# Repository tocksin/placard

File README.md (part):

# Placard
## PLA computer
This project is a computer designed using some Programmable Logic Arrays (PLA) 
or Programable Array Logic (PAL) or Programmable Array Devices (PLD) chips.  
This started as a pure 7400-series chip computer, but changed over to using 
some PLA/PLDs to increase the usability while not greatly increasing the chip 
count.  The first PLA was created in 1970 by Texas Instruments.  The PAL was 
created in 1978 by Monolithic Memories which is owned by Lattice Semi today. 
There are some differences between the three types of chips, but this project 
isn't going to distinguished between them.

The design documents are in [docs/](docs/README.md), grouped by subject.

## Project goals
The project has some hard-goals to maintain:
- Use only through-hole chips similar to the 7400-series DIP chips (or PLA of course)
- Use only active production chips.  No hunting sketchy websites for parts.
- Design true von Neumann CPU from scratch.  No Harvard.  Bare-metal programming on the computer is a must (native compiler).
- Have a video output.  The video standard is open, but probably a legacy output (VGA/Composite/etc).
- Make the instruction set "fun" to program.  This means no racing the beam to draw the screen.  Counting instructions is not fun.
- A PS/2 keyboard and mouse, read by the machine's own PLD receiver.  No USB.
- Native storage capabilities.  Need to be able to save/load programs as you create them on the computer.

## Block diagram
Each block shows how many chips it uses (33 and a 3.3 V regulator on the main board; the expansion and cartridge slots add none, the cartridge itself has 5).  See [docs/architecture/CHIPS.md](docs/architecture/CHIPS.md) for the parts.

The drawing is made by `src/scripts/gen_block_diagram.py` (CPU on the left, memory, I/O and audio in the middle, video on the right); rerun it when the design changes.

The I/O circuitry (SNES pads, SD card, PS/2 keyboard and mouse) is drawn as a schematic in
[docs/architecture/IO.md](docs/architecture/IO.md#schematic) (`schematics/placard_io_schematic.png`).
The audio circuitry (sample read, DAC register, R-2R ladder, audio line out jack) is drawn in
[docs/sound/SOUND.md](docs/sound/SOUND.md#schematic) (`schematics/placard_video_audio_schematic.png`).

The real schematic and PCB layout are a KiCad project in [kicad/](kicad/).

To build a board one chip at a time, testing each with a multimeter as it goes in, follow [docs/hardware/BRINGUP.md](docs/hardware/BRINGUP.md); it has a bring-up test ROM that checks the CPU and memory and shows the I/O on the screen.

## Memory Map
The Placard has 64kB of memory arranged in a 16-bit address bus and 8-bit databus.  The video RAM starts at x6020 and ends at xFFFF, and each row's mode byte (color mode and line repeat) is at x5A20 + row.  There is a 64kB RAM and a 64kB ROM behind the same addresses.  The address space is divided into eight 8kB sections, and a write-only map register at x5000 picks whether each section reads from the RAM or the ROM.

- **Writes always go to the RAM**, even in a section mapped to ROM.  The write strobe (/WE) is not decoded by address, so a write in the I/O window x5000-x53FF also lands in the RAM underneath it.
- **The map register** is a CD74ACT273E clocked by /MAP_WR from the I/O decode PLD; it latches the source bus at the end of the write.  Bit n = 1 makes section n read from RAM, 0 from ROM.  Bit 2 maps x4000-x4FFF and x5400-x5FFF, because x5000-x53FF is the I/O window.  It is write only, so software keeps a copy of the last value it wrote.
- **At power-up every section reads as ROM.**  RUN from the ROM cartridge holds the register's /MR low while the cartridge loads its SRAM and the CPU is held, so the CPU boots from ROM ([docs/architecture/ROM.md](docs/architecture/ROM.md#loading-the-cartridge)).
- **x5000-x53FF is the I/O window.**  The memory control PLD keeps both the RAM and the ROM off the bus there, so I/O always has priority.
- **Only `[Y,X]` reaches the I/O window**; `[0,D]` and `[0,X]` only address the zero page.
- **Video reads always read the RAM** (memory control PLD); only CPU reads follow the map.  The CPU can run code from the ROM under the video area while the screen shows the RAM, and a program that wants to read the video RAM maps that section to RAM.
- **The ROM is grouped by 8 KB section.**  The machine's 32K ROM (x8000-xFFFF, read at x0000-x7FFF too) holds the boot loader, the library, BASIC and a loader that runs the DOS and programs from the SD card, and each map section holds one kind of thing: section 7 what almost every program uses (jump table, core routines, PS/2 keyboard, pads, mouse, line input), section 6 the files (SD card driver, FAT reader and writer), section 5 BASIC, section 4 the loader, sound driver and font.  A program that maps a section to RAM gives up just that; the font is read through a zero page pointer (`FONT_PG`), so a program can put its own font anywhere.  The library runs in place.  The boot loader copies the library's RAM code to x1F00, gives each expansion card a chance to run its own boot code (like the Apple II), then maps sections 0 and 2 to RAM (map = 05) and starts the loader.  A development ROM (64K cartridge) adds one program in the first 32K, run in place at x6000-x7FFF and x2000-x3FFF, or copied to RAM x0000 for the older demos.  See [docs/architecture/ROM.md](docs/architecture/ROM.md) and [docs/software/DOS.md](docs/software/DOS.md).
- **After a map write**, the next instruction must not be fetched from a section whose map bit that write changed, unless the ROM and RAM hold the same byte there (the new map arrives 2.6 ns too late for that fetch).  Copying the ROM into the RAM underneath and then switching the section is safe.  See [docs/timing/TIMING.md](docs/timing/TIMING.md#video-and-the-rest).

The memory control PLD (`ATF22V10_MEM_CTRL.pld`) makes /ROM_OE and /RAM_OE from the address, the map, RW and PIXEL_ENABLE, using only the low half of each clock.  The RAM's /WE comes from the Sync PLD, off an early tap of the clock ([docs/timing/WE_TIMING.md](docs/timing/WE_TIMING.md)).  The I/O decode PLD (`ATF22V10_IO_DECODE.pld`) makes the upper RAM/ROM chip select (/CE_HI) and the I/O strobes.

The RAM is two AS7C256C-15PCN (32K × 8, 15 ns) chips.  The ROM is two more AS7C256C-15PCN on the ROM cartridge, loaded at power-up from two AT28C256 EEPROMs by the cartridge while it stalls the CPU ([docs/architecture/ROM.md](docs/architecture/ROM.md#loading-the-cartridge)).  See [docs/architecture/CPU.md](docs/architecture/CPU.md#memory-parts) and [docs/timing/TIMING.md](docs/timing/TIMING.md).

| Address | Map bit | Function  |
|---------|---------|------|
| x0000-x1FFF | 0 | RAM/ROM (zero page, program variables, library RAM code at x1F00; ROM: reset jump) |
| x2000-x3FFF | 1 | RAM/ROM (development ROM: program) |
| x4000-x4FFF | 2 | RAM/ROM (program data; FAT variables and buffer at x4D00-x4FFF) |
| x5000-x53FF | none | I/O window (see below) |
| x5400-x5FFF | 2 | RAM/ROM (mode bytes at x5A20-x5BFF, audio buffer at x5DF3-x5FFF) |
| x6000-x7FFF | 3 | RAM/ROM (Video Memory from x6020; development ROM: program from x6000) |
| x8000-x9FFF | 4 | RAM/ROM (Video Memory; ROM: vectors x8000, loader and the end of BASIC x8100, sound driver x9200, font x9700, LIB_RAM copy x9F00) |
| xA000-xBFFF | 5 | RAM/ROM (Video Memory; ROM: BASIC) |
| xC000-xDFFF | 6 | RAM/ROM (Video Memory; ROM: files: SD card driver xC000, FAT reader xC800, FAT writer xD600) |
| xE000-xFFFF | 7 | RAM/ROM (Video Memory; ROM: PS/2 keyboard, pads, mouse, line input, menu hook, slot helpers, core routines xF400, jump table xFB00, boot loader xFD00) |

The drawing is made by `src/scripts/gen_memory_map.py`; rerun it when the map changes.

### I/O window
Each I/O page has its own select from the I/O decode PLD (revision 07), made straight from the address and valid about 13 ns into the clock.  A write is the select with /WE: devices latch the source bus on the rising edge at the end of /WE.  A read is the select with Q0 low (the LOAD_MEM clock, when the CPU latches the bus into D), and nothing waits for STALL.  The shared port is described in [docs/architecture/IO.md](docs/architecture/IO.md) and the expansion slots in [docs/architecture/EXPANSION.md](docs/architecture/EXPANSION.md).

| Address | Select | R/W | Function |
|---------|--------|-----|----------|
| x5000-x50FF | /P0 (write: /MAP_WR from the Sync PLD) | W | ROM/RAM map register (built) |
| x5000-x50FF | /P0 and Q0 | R | Video line counter, V9:V2 (built) |
| x5100-x517F | /EXP1 | R/W | Expansion slot 1 |
| x5180-x51FF | /EXP3 | R/W | Expansion slot 3 |
| x5200-x52FF | /PORT and /WE | W | Shared port latch (port PLD registers): SD card SCK, MOSI and /CS, SNES pad clock and latch, PS/2 lines; a write to x5202/x5203 also re-arms the PS/2 receiver |
| x5200-x52FF | /PORT and Q0 | R | Shared port: SD MISO and the free PS/2 clock (x5200), SNES pad data (x5201), PS/2 receiver byte (x5202) and ready flag (x5203) |
| x5300-x537F | /EXP2 | R/W | Expansion slot 2 |
| x5380-x53FF | /EXP4 | R/W | Expansion slot 4 |

### Sound
The video circuit reads one 8-bit sample per scan line from x5DF3-x5FFF (525 bytes, one frame) and plays it through a 74HCT574 and a resistor ladder DAC, at the line rate of 31.47 kHz.  80h is silence.  The library's sound driver (`snd_update` once a frame, with `snd_tone`, `snd_beep`, `snd_note`, `snd_noise` and `snd_play`) refills the buffer behind the line being played.  See [docs/sound/SOUND.md](docs/sound/SOUND.md).

### Video line read
A read anywhere in x5000-x50FF returns the upper 8 bits of the video line counter, V9:V2.  The V counter in the V Counter PLD counts 499 to 1023, and one 74F541 enabled by /P0 and Q0 puts V9:V2 on the data bus.  The ROM/RAM map register shares the page but is write only, so there is no conflict.  Read it with `ld 0x50, y` then `ld [y,x], ac`.

- **It is a single byte**, so it can't tear between reads.
- **Resolution is 4 lines** (128 us).  Visible rows start at V = 544, so `row / 4 = value - 136`.  A value below 136 means vertical blanking.
- **There is no frame counter.**  Software keeps time by polling: each time the value goes down (from 255 back to 124), a frame has passed.  At the FPGA's 25.000 MHz clock a frame is 525 lines, about 16.8 ms (59.5 Hz).
- **Software must poll at least once per frame**, or it misses a wrap.  Elapsed time is then frames x 16.8 ms plus the line position for finer detail.

## Video
The video is designed to be 640x480 VGA 60Hz standard.  This means a 25.175 MHz clock.  This requires two counters: a horizontal and vertical.  They count 800 and 600 pixels.  This needs a 10-bit counter for each.  The counters form the RAM address space to read the pixel values.  The video memory is organized in a non-traditional way with H,V instead of V,H.

### Line repeat
Bits 3:2 of a row's mode byte make each byte of video memory show on 1, 2 or 4 lines (640 × 480, 240 or 120).  A full 2x screen leaves 20 KB of the video area free (the even pages x60, x62 ... xFE) and a full 4x screen 30 KB.  The audio slot PLD remaps four row address bits, so no chips were added.  See [docs/video/VIDEO.md](docs/video/VIDEO.md#line-repeat).

### Text demo
`src/scripts/text_demo.asm` draws a demo screen with the CPU and keeps a test running on it: 80 column text (2 colors, 1x, on row tints: a blue status panel and a rainbow raster bar that bounces behind the text), a 16 color band (4 bpp, 4x), 40 column text (2 bpp, 2x) and a 256 color band (8 bpp, 4x) with "256" in shades of red, blue and green and a turning rainbow ring.  Each frame it tests one page of RAM (85 pages: x0100-x1EFF, x2000-x4FFF, x5400-x59FF and x5C00-x5CFF, 14 patterns each, with a progress bar, pass and error counts) and updates a frame counter, an uptime clock, a spinner, a turning color wheel, the ring and a message that scrolls a pixel a frame.  It runs from the SD card (`TEXT.PLC`, `gen_text_demo_sd.py`, in the demo menu), and `src/scripts/text_demo_sim.py` runs and checks it in the simulator (`--gif` makes an animation).  `gen_text_demo_sd.py` makes the SD card version (`TEXT.PLC`, in the demo menu), whose RAM test covers only the RAM the program leaves free ([docs/software/MENU.md](docs/software/MENU.md#the-text-demo-on-the-card)).

### DOS, BASIC and demo menu
The machine ships the 32K ROM image (`src/scripts/rom32.masm`, `build\rom32.bat`): the boot loader, the library, PLACARD BASIC (a 16-bit integer BASIC with strings, graphics, sound and SAVE/LOAD on the card, [docs/software/BASIC.md](docs/software/BASIC.md)) and a loader that runs `.PLC` programs from the SD card.  The DOS is one of those programs (`DOS.PLC`, `src/scripts/dos.masm`).  At power-up the loader runs the program named in `BOOT.CFG`, or the DOS's file browser (hold Esc) that runs, deletes and picks the boot program, with a command line for `LOAD` and `SAVE` of memory as files.  With no card, or no `DOS.PLC` on it, BASIC starts.  Ctrl+B in the browser starts BASIC.  The demo menu is one of those programs (`MENU.PLC`, `src/scripts/menu.masm`): the CPU test, pi, Mandelbrot, the Game of Life, the Boing ball, the 3D ships, the ray caster, the side scroller, the textured ray caster and the text demo run in turn, each until it is done or for 2 minutes (Mandelbrot 3); Esc in any program shows the menu (Up / Down and Enter, or 1-9 and 0), a program picked there runs until Esc, and after 2 minutes with no key the menu goes back to running them in turn.  The `sdcard/` folder holds the files for the card; `src/scripts/test_dos.py`, `test_menu.py` and `test_basic.py` check them in the simulator; the `.BAS` files on the card are BASIC examples.  See [docs/software/DOS.md](docs/software/DOS.md), [docs/software/MENU.md](docs/software/MENU.md) and [docs/architecture/ROM.md](docs/architecture/ROM.md#the-32k-image).

### Game demos
Four demos show what the CPU can do with no sprite or collision hardware.  The first three are written by a Python generator (the tables, the unrolled drawing code and a bit-exact model of the picture), and each has a simulator test that checks every frame against the model.

`sdcard/RAYCAST.PLC` (`gen_raycast.py`, which writes `src/scripts/raycast_sd.asm`) is a ray caster: an 80 × 112 view at 8 bpp (4x line repeat) of a maze with shaded, two-tone walls and a dithered floor and ceiling, walked by a demo script until a key or pad button takes over (arrow keys or SNES pad 1: Up / Down walk, Left / Right turn).  A view takes 143k-170k clocks (a column about 2,000), so it runs at the full 60 views a second using under 40 % of each frame.  It is in the demo menu and `src/scripts/test_raycast_sim.py` checks it.

`sdcard/RAYTEX.PLC` (`gen_raycast_tex.py`, with `RAYTEX.OVL`) is the same maze and demo walk with textured walls, in the style of Wolfenstein 3D: seven 32 × 32 textures drawn by the generator (stone, brick, wood, riveted metal, mossy stone, a circuit board with a 22V10 and a framed Mandelbrot picture), y sides darker than x sides and four levels of distance shading.  Each column finds where the ray hit the wall (two 8 × 8 multiplies), copies that texture column through a shading table into zero page, and draws the wall with a compiled scaler: one unrolled routine per wall height that stores the right texel into each cell.  A view takes 229k-261k clocks (about 3,000 a column), so it still runs at 60 views a second, with room left for sprites.  T turns the textures off (one flat, shaded color a wall) and on again.  `src/scripts/test_raycast_tex_sim.py` checks it.  It is in the demo menu: its textures and scalers go into the video RAM the screen leaves free ([docs/software/MENU.md](docs/software/MENU.md#the-ray-casters-and-the-scroller-on-the-card)).

`sdcard/SCROLLER.PLC` (`gen_scroller.py`, with `SCROLLER.OVL`) is a side-scrolling platformer at 160 × 112, 4 bpp: three parallax bands (clouds, mountains, hills at 1/8, 1/4 and 1/2 speed) over a tiled level, with a robot that runs, jumps, collects coins and stomps slimes, all at 60 frames a second.  The background is redrawn every frame by unrolled strips, top to bottom ahead of the beam, so nothing has to be erased.  The sprites are compiled: each frame of art is its own routine in RAM that stores its bytes (masked where a byte is half transparent) straight into video memory.  Background and sprites take about 93k of the 420k clocks in a frame.  The demo player plays until a key or pad button is pressed (arrow keys or SNES pad 1: Left / Right to run, Up, Space or pad B to jump).  `src/scripts/test_scroller_sim.py` checks it.  It is in the demo menu: its background strips go into the video RAM the screen leaves free ([docs/software/MENU.md](docs/software/MENU.md#the-ray-casters-and-the-scroller-on-the-card)).

`sdcard/WIRE3D.PLC` (`gen_wire3d.py`) is an Elite-style 3D demo and benchmark: six convex ships tumbling in 3D at 320 × 240, switching every 20 seconds between wireframes with hidden lines removed and filled, shaded faces painted far to near.  Quarter-square multiplies, projection by log tables, Elite's face test in each ship's own space, XOR lines erased by drawing them again, and filled ships erased by blanking only what their new outline does not cover.  Six ships is the limit with margin: filled mode stays above 20 fps (seven ships touch 20), wireframes hold the 30 fps cap with half the CPU spare.  [docs/software/WIRE3D.md](docs/software/WIRE3D.md) has the measurements; `src/scripts/test_wire3d_sim.py` checks every frame against a model.

`sdcard/PLAY.PLC` (`src/scripts/play.masm`) plays `DEMO.SNG` with the music player (`src/scripts/placard_mus.masm`, [docs/sound/MUSIC.md](docs/sound/MUSIC.md)): four SID-style voices (pulse with a swept width, saw, triangle, noise or a custom wave, each with an ADSR envelope) and a fifth for sound effects, driven once a frame by patterns, instruments with wave and pulse programs, and effects (arpeggio, slides, portamento, vibrato, volumes, speed), mixed into the line-fetched audio buffer at 15.7 kHz on about 20 % of the CPU.  `mus_tool.py` turns a song written as text (`src/music/demo.mus`, which shows off every feature in 54 seconds) into the `.SNG` file and a WAV, and `test_mus.py` checks the player against its Python model sample for sample.  `sdcard/TRACKER.PLC` (`tracker.masm`, with `TRACKER.OVL`) is the editor on the machine: the orderlists, the four patterns side by side, the instruments and the wave and pulse tables on an 80 x 30 screen, played while you edit, loaded from and saved to `.SNG` files on the card.

`sdcard/BOING.PLC` (`gen_boing.py`) is the Amiga's Boing Ball: a red and white checkered ball, tilted 17 degrees, spinning and bouncing in front of a purple grid with its shadow on the wall, at 160 × 120, 4 bpp.  It holds 60 fps on about a third of the CPU.  The Placard has no palette registers for the Amiga's color-cycling trick, so the spin is 8 phases worked out ahead of time, and each frame redraws only the rows the ball and its shadow touch.  It draws from a clean copy of the background kept in the video RAM that 4x rows leave free, top to bottom and ahead of the beam.  [docs/software/BOING.md](docs/software/BOING.md) has the details and `src/scripts/test_boing_sim.py` checks every frame against a model.

`sdcard/SCRAP.PLC` (`src/scripts/scrap.masm`, `gen_scrap.py`, with everything else it reads, `SCRAP.OVL`, the swap files and the part text, in `sdcard/SCRAP/`) is SCRAPWRIGHT, an original top-down ship salvage game in progress: run it from the DOS's file browser.  You walk from a salvage tug docked to a derelict on one 96 × 64 map: 20 × 12 cells of 8 × 16 pixel art in 4 bpp, and a 1 bpp panel that shows the cell under the PS/2 mouse (name, damage bar, info and an action menu).  Phase 3 adds salvage and air: uninstall the wreck's parts with the plasma cutter (the tug's by hand), carry three (two hands and your back, shown on an inventory screen), install them from there or from the deck, in the tug or in a wreck, take its walls, decks and doors out and put them back wherever you like (the rooms and their air are worked out again; broken walls leak), repair what is damaged (anything broken is drawn cracked; nothing goes on a broken deck), lay power conduit, fit a comms antenna and a radar outside, feed the air from an O2 tank through a pump and the thrusters' nitrogen through an intake, with six skills (mechanical, electrical, nuclear, computers, hydraulics, suit) that set how long each job takes and grow as you use them, take your suit off to work quicker (and mind the vacuum), and watch your suit's O2: every room holds its own air, open doors share it, a hull breach drains it, and the warnings go from caution to blacking out.  The navigation mode has begun: NAVIGATE at the helm opens a sector map (a station on an asteroid and derelicts to visit, the tug a triangle that turns with its heading, a zoom in doubling steps, a target picked with the mouse or Tab) above a boxed control panel (flight, propulsion, and the target's range, radar return, registry and the tug's speed toward it and across), where you undock, fly the tug on its thrusters' nitrogen (its mass and thrust from the parts you built in), and dock again; it keeps cruising while you walk, and flying into the wreck damages the tug.  `test_scrap_sim.py` checks it ([docs/software/SCRAP.md](docs/software/SCRAP.md)).

`sdcard/SKYWARD.PLC` (`src/scripts/gen_skyward.py`, with its courses in `sdcard/SKYWARD/`) is Skyward Tobi, a port of *Skyward Tobi 4*, an NES platform game by Mark Szlemko (MIT License): the 21 side-scrolling courses of its two worlds, Breezy Isle and Gusty Mesa, at 160 × 112, 4 bpp, on the scroller's engine with five rows of tiles, each course a file read from the card.  Tobi runs, jumps and glides, lands on Bumblers, Buzzbees and Shellbys (and sends their shells sliding), keeps clear of Spindles and Snapjaws, rides lifts, air vents and bounce drums, opens crates for a Sky Berry, an Ember Pepper, a Glide Feather or the Tengu Geta, collects Stunt Medals and meets Captain Squall in his two forts and Baron Rook in Crow Keep and Dust Keep.  Mark's songs play on the four-voice music player, and his nine story pictures open and close the game.  Run it from the DOS's file browser (arrow keys or SNES pad 1; Up, Space or pad B to jump).  `test_skyward_sim.py` plays it through with a bot ([docs/software/SKYWARD.md](docs/software/SKYWARD.md)).

`sdcard/LAMP.PLC` (`src/scripts/gen_lamp.py` and `lamp_code.masm`, with its rooms and tile sets in `sdcard/LAMP/`) is Lamplighter, an original exploration platform game in progress (music, title and saving still to come): Wick, a beacon keeper, climbs down through the hollow moon Cairn to relight its great lamp.  Rooms of up to 32 × 16 tiles scroll both ways at 160 × 112, 4 bpp, and join at their edges into a world that branches from a central shaft; a room is a 1 KB file read from the card as Wick enters it.  The playfield is redrawn every frame, tile row by tile row just behind the beam, each tile one jump into unrolled code, and compiled sprites go over it.  The whole world is in (34 rooms): the hub, the Glasswort Gardens, the Slagworks, the flooded Brine Vaults, and the Orrery under a seal that the three bosses open, with the last boss, the Snuffer, guarding the Great Lamp: walking, jumping, a lantern that fires sparks, doors that open to a shot, creatures that walk, fly, hop, spit and drop, energy, and things to find (the Burrow Rig to crawl through ducts, the Updraft Bellows for a second jump in the air, the Kiln Charge whose blast breaks sooted blocks, the Ballast Boots for walking under water, Oil Flasks, and the Ash Sail, the Cinder Coat and the three-way Wide Flame that the bosses Bramblejaw, Clinker and Old Gulper guard).  Every boss can be reached and beaten with nothing collected; what is found makes the way shorter and the fight easier.  Run it from the DOS's file browser (arrow keys or SNES pad 1; Z, Space or pad B to jump, X or pad Y to fire, Down to crawl).  `test_lamp_sim.py` plays it with a bot that plans its route by searching a Python model of the rules, and compares the program with that model on every frame ([docs/software/LAMPLIGHTER.md](docs/software/LAMPLIGHTER.md)).

## Standard library
`src/scripts/placard_lib.asm` holds subroutines for new programs: 16-bit
arithmetic, multiply and divide, memory fill and copy, random numbers, frame
timing, pixels, a text console with line input, the keyboard, SNES pad,
PS/2 mouse and SD card drivers, a FAT16/FAT32 file reader, a sound driver
and expansion card lookup.  It also sets the calling convention, the
software stack and the zero page variable map (`zeropage.asm`).  See
[docs/software/LIBRARY.md](docs/software/LIBRARY.md).

## Emulator
Open `web/index.html` in a browser to run the PLACARD without hardware: the
32K ROM (or one you load), an SD card (the `sdcard/` folder, a folder of
your own or a card image), the screen, sound, keyboard, mouse and game
controllers, at the real clock rate.  No server is needed.  See
[docs/software/EMULATOR.md](docs/software/EMULATOR.md).

## Building and loading a program
The `build` folder has one Windows batch file per assembly program
(`cpu_test.bat`, `test_video.bat`, `mandelbrot.bat`, `pi_spigot.bat`,
`game_of_life.bat`, `lib_demo.bat`, `io_demo.bat`) and `rom32.bat` for the
released 32K ROM.  The larger demos run from the SD card only.  Each one assembles
`src/scripts/<program>.asm` (customasm, or `placard_sim.py` if customasm is not
on the PATH), writes the RAM initialization files `src/hdl/ram.mem` (main
RAM) and `cart_ram.mem` (cartridge SRAM), random bytes like a real SRAM at
power-up (`gen_random_ram.tcl`), and the cartridge EEPROM image
`src/hdl/rom.mem` (boot loader, standard library and font, and the program,
`gen_rom.tcl`; see [docs/architecture/ROM.md](docs/architecture/ROM.md)), runs
Vivado in batch mode through synthesis, implementation and bitstream, and
programs the Basys 3 over JTAG.  Any other program builds with
`build\build_and_load.bat <program>`.  Add `noasm` (e.g. `cpu_test.bat noasm`)
to skip assembly and use the existing `.hex` file.  Vivado is found on the PATH or under
`C:\AMDDesignTools` / `C:\Xilinx`; set `VIVADO` to the full path of
`vivado.bat` to pick a version.  Logs go to `build/logs`; the Vivado Tcl scripts
behind the batch files are in `build/tcl`.
Add `fast` (e.g. `mandelbrot.bat fast`) to change only the memory contents:
the new `ram.mem`, `cart_ram.mem` and `rom.mem` are written into the last implemented bitstream with
`updatemem` (block RAM map from `build/tcl/write_mmi.tcl`), so synthesis and
implementation are skipped.  It needs one full build first, and a full build
again after any HDL or constraint change.  The first `fast` run after a full
build checks the block RAM map by putting the full build's own image back into
its bitstream; if that does not give the same bitstream it stops with an error.
`build\download_latest.bat` programs the board with the newest bitstream in
`project/placard.runs/impl_1` (`basys_top.bit` or `basys_top_fast.bit`) without
rebuilding.
The batch files play a sound when they finish (`build\ding.bat`): the
Windows "Ding" when the build worked and "Critical Stop" when it failed.
Set `PLACARD_QUIET=1` to turn it off.

### Vivado project
The Vivado project (`project/placard.xpr` and everything else in `project/`)
is not kept in git, because Vivado rewrites the `.xpr` every time it opens it.
`build/tcl/create_project.tcl` makes it from the sources in `src/`, with the
part, file list, testbench and run settings.  The first build makes it by
itself; to open the project in the GUI after a fresh clone, run
`build\create_project.bat` once.  Every `.vhd` file in `src/hdl` is a design
source, so after adding or removing one run `build\create_project.bat force`.
Testbenches and other settings are listed in `create_project.tcl`; change them
there, because a change made only in the GUI is lost the next time the project
is made.
`src/hdl/ram.mem`, `cart_ram.mem` and `rom.mem` are not kept in git either; every
build makes them, and `create_project.tcl` makes the default images if they
are missing.  A project made before the ROM had its own file lists
`video_ram.mem`; the next build swaps it for the new files, or run
`build\create_project.bat force`.

## License
Placard is open hardware and open software.  Each kind of work has the license written for it:

| Part | License |
|------|---------|
| Hardware: the KiCad boards and schematics (`kicad/`, `schematics/`), the PLD equations and VHDL (`src/pld/`, `src/hdl/`, `src/sim/`) and the case (`case/`) | [CERN-OHL-S v2](LICENSES/CERN-OHL-S-2.0.txt) |
| Software: the ROM, BASIC, DOS, demos, games, tools and emulator (`src/scripts/`, `src/music/`, `sdcard/`, `web/`, `build/`) | [GPL v3 or later](LICENSES/GPL-3.0-or-later.txt) |
| Documentation and images (`README.md`, `docs/`, `reference/`) | [CC BY-SA 4.0](LICENSES/CC-BY-SA-4.0.txt) |

All three are share-alike: you may build, change and sell the design, and you pass your changes on under the same license.  A program you write for the Placard, loaded from the SD card or a cartridge, is your own work under any license you choose.  [LICENSE](LICENSE) has the full folder list and the third-party parts (KiCad library copies, the Digilent debouncer, the Inter lettering in the logo).

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
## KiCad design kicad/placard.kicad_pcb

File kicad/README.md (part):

# KiCad project

Date: 2026-11-11

The Placard schematic and PCB layout, one KiCad project for the main board
and one for each cartridge.  The files are saved by KiCad 9, so open them
with KiCad 9 or newer.  Board revisions are in
[docs/hardware/RELEASES.md](../docs/hardware/RELEASES.md): rev A is the
board as ordered (git tag `rev-A`), and the files here are the working
rev B.

| File | What it is |
|------|------------|
| `placard.kicad_pro` | the project; open this in KiCad |
| `placard.kicad_sch` | the schematic's root sheet (A3): one box per sheet, laid out like the block diagram |
| `power.kicad_sch` ... `expansion.kicad_sch` | the ten sheets (power and clock, control, PC and address mux, ALU and registers, data bus, memory and I/O decode, video timing, video and audio out, shared port, expansion slots), docs/hardware/SCHEMATIC_PLAN.md |
| `cartridge_64k/` | the 64K ROM cartridge (5 chips), its own project (`cartridge_64k.kicad_pro`, one sheet and a routed 4-layer board), using the same `lib/` |
| `cartridge_32k/` | the 32K ROM cartridge (3 chips), its own project (`cartridge_32k.kicad_pro`, one sheet and a routed 4-layer board), using the same `lib/`; mounting hole H1 at the same place as on the 64K board |
| `placard.kicad_pcb` | the main board, routed: 4 layers (F.Cu, In1.Cu = GND, In2.Cu = VCC, B.Cu) |
| `lib/placard.kicad_sym` | PLD symbols: `ATF22V10C` (generic) and one `ATF22V10C_<name>` per `.pld` file, with its pin names |
| `lib/placard_parts.kicad_sym` | other project symbols: `AS7C256C` SRAM, `Expansion_Slot`, `Cartridge_Slot`, `SNES_Pad_Socket`, `PS2_Dual_Stacked`, `USB_C_Power` |
| `lib/placard_std.kicad_sym` | copies of the stock KiCad symbols the sheets use (74xx, R, C, D, connectors, regulator, the cartridge EEPROM `28C256`, and the power symbols `+5V`, `GND`, `+3V3`, `GNDA`, `PWR_FLAG`) with larger pin text, written by `src/scripts/gen_kicad_std.py` |
| `lib/placard.pretty/` | project footprints: the main board's connectors and switches (written by `src/scripts/gen_kicad_connectors.py`), and kit versions of KiCad's DIP socket footprints (`DIP-nn_..._Socket_Puller`: chip-puller room on User.Eco1, part number in silkscreen) and of the axial resistor (`..._Value`: value in silkscreen), written by `src/scripts/gen_kicad_kit_footprints.py`, and copies of the KiCad 9.0.6 footprints the boards use (capacitors, diodes, LED, pin header, oscillator, TO-92, SIP resistor array, mounting holes, net tie; KiCad 9 format), written by `src/scripts/gen_kicad_stock_footprints.py` |
| `lib/placard.3dshapes/` | 3D models (STEP) for the connectors, switches and polyfuse, named after their footprints and referenced as `${KIPRJMOD}/lib/placard.3dshapes/...`, so they show in any KiCad version without a 3D library path; written by `src/scripts/gen_kicad_3d_models.py` (CadQuery), which also copies in KiCad's own models for SW2, J7 and J13, and KiCad's models for the stock, socket and resistor footprints, copied by `src/scripts/gen_kicad_stock_footprints.py` |
| `sym-lib-table`, `fp-lib-table` | point KiCad at the project libraries |
| `fab/` | the rev A Gerber and drill files as ordered ([fab/README.md](fab/README.md)) |

The main board is 290 x 215 mm (290 wide, the keyboard's width; 215 deep, so
kit builders have room), 4 layers, placed and routed.

The back edge carries USB-C power, audio line out, VGA and the stacked PS/2;
the left side the power switch, reset button and SD card; the front edge the
two SNES ports.  The cartridge and the four expansion cards stand up
through the case top.  Every DIP sits in a socket footprint with 2.5 mm of
chip-puller room clear past each socket end, and Cn sits beside Un.
`src/scripts/gen_board_pictures.py` draws the two pictures (and the
cartridge pictures in [EXPANSION.md](../docs/architecture/EXPANSION.md))
from the board files without changing them; rerun it after a layout change.

The board file is edited in KiCad and by the autorouter, so it is the
source.  `src/scripts/gen_kicad_pcb.py` made the first outline and placement
and `src/scripts/gen_kicad_cart_pcb.py` the cartridges' placement; do not
run either on the boards now (the cartridge script leaves an existing board
alone unless given `--force`).  The first placement drawings are in
[docs/archive/](../docs/archive/README.md).

The footprints KiCad has no part for (cartridge slot, expansion slots,
PS/2, SNES, the power switch, the relay) are written by
`src/scripts/gen_kicad_connectors.py`.  The SNES sockets were measured from
the part; the others are drawn from typical dimensions for the part family,
so check them against the parts when the rev A boards arrive.
Their 3D models (`src/scripts/gen_kicad_3d_models.py`) are drawn at typical
dimensions too, with the leads put on the footprint pads.  J4 (SD), J7 (VGA),
F1 and SW2 use project copies of KiCad's footprints (`placard:` library) only so
they can point at the project's models; the pads are KiCad's.
The schematic rules (which chips go on which sheet, numbering, and how
the sheets are drawn) are in [docs/hardware/SCHEMATIC_PLAN.md](../docs/hardware/SCHEMATIC_PLAN.md).  Parts and U-numbers come from
[docs/architecture/CHIPS.md](../docs/architecture/CHIPS.md); the PLD pinouts come from the `.pld` files
in `src/`.

Every part carries Manufacturer and MPN fields (empty where no part number
is chosen yet), set from the `MPN` table in `src/scripts/gen_kicad_schematic.py`,
so KiCad's BOM export lists them.  `src/scripts/gen_bom.py` writes one grouped
bill of materials per assembly (main board, 64K and 32K cartridges, case),
indexed in [docs/bom/BOM.md](../docs/bom/BOM.md), each as .md and .csv, including the
bare PCBs, sockets, shells and screws that are not on the schematic.

Backups, autosaves, lock files, `*.kicad_prl` (per-user view settings) and
`fp-info-cache` are git-ignored.

## PLD symbols

`src/scripts/gen_kicad_symbols.py` writes `lib/placard.kicad_sym` from the
`PIN` statements in `src/pld/*.pld`; rerun it after changing a PLD's pins
(it overwrites the whole library).  The pins are placed for the schematic,
not in pin-number order: the script's `LAYOUT` table puts inputs on the
left and outputs on the right, buses together in bit order, and each
function's pins in their own group.  Where one PLD does two unrelated jobs
(the audio PLD's /AC_SEL, the port PLD's pad read, the memory control's
RUN input) a dashed line across the box separates them.  Active-low pins are
`/NAME`, VCC (24) is on top and GND (12) underneath, unused pins are `nc`
(no-connect type), and the `.pld` file name is under the part number.  The
script stops if a `.pld`'s pins and its `LAYOUT` entry no longer match.
Each symbol has the footprint `Package_DIP:DIP-24_W7.62mm` and the
ATF22V10C datasheet link.

## Other symbols

`src/scripts/gen_kicad_parts.py` writes `lib/placard_parts.kicad_sym`, in
the same style, for the parts KiCad's libraries do not have: the AS7C256C
SRAM, the expansion slot (Molex 87715-9106 as the cartridge slot, contacts A1-A32 and B1-B32)
and the cartridge slot (Molex 87715-9106, 2 x 32 keyed, contacts A1-A32
and B1-B32), as in EXPANSION.md, with the +5 V and GND contacts stacked on
one pin each, the SNES pad socket (IO.md) and
`USB_C_Power`, the 5 V input: a power-only 6-contact USB-C receptacle
(GCT USB4125, footprint `placard:USB_C_Receptacle_GCT_USB4125_6P_HandSolder`:
KiCad's USB4125 footprint with the SMD pads 1.5 mm longer for the iron, made by gen_kicad_connectors.py)
with a 5.1k resistor from CC1 and from CC2 to GND so a charger gives 5 V.  Make
changes in the script, since rerunning it overwrites the library.

Every symbol, footprint and 3D model the sheets and boards use is in `lib/`
(since 2026-10-26): the projects' library tables list only the placard
libraries, so the project opens the same on any PC and DRC/ERC find nothing
missing or different from its library.  The parts below started as KiCad
library parts and are used through their copies in `placard_std` and
`placard.pretty`:

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
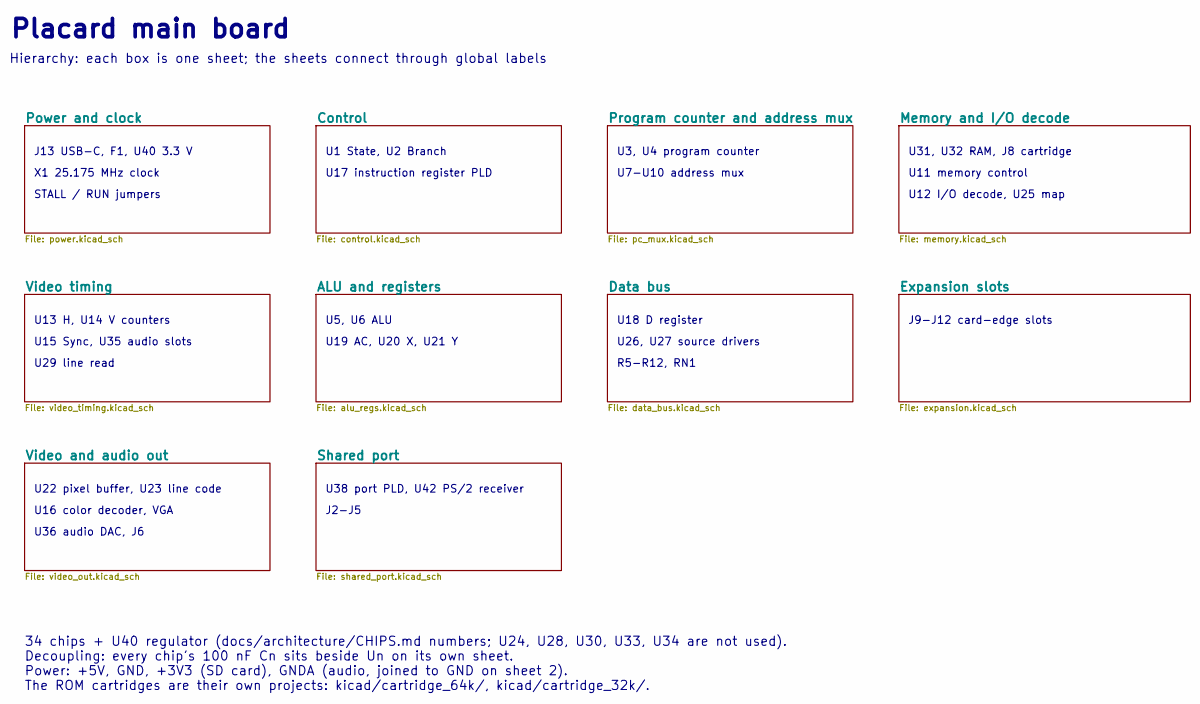
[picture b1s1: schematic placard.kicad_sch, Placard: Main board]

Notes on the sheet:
X1 25.175 MHz clock
U7-U10 address mux
U12 I/O decode, U25 map
J13 USB-C, F1, U40 3.3 V
U19 AC, U20 X, U21 Y
U3, U4 program counter
U5, U6 ALU
34 chips + U40 regulator (docs/architecture/CHIPS.md numbers; U24, U28, U30, U33, U34 are not used).
Power: +5V, GND, +3V3 (SD card), GNDA (audio, joined to GND on sheet 2).
J9-J12 card-edge slots
U11 memory control
STALL / RUN jumpers
J2-J5
Hierarchy: each box is one sheet; the sheets connect through global labels
U26, U27 source drivers
U13 H, U14 V counters
U29 line read
U36 audio DAC, J6
U1 State, U2 Branch
R5-R12, RN1
The ROM cartridges are their own projects: kicad/cartridge_64k/, kicad/cartridge_32k/.
U15 Sync, U35 audio slots
U31, U32 RAM, J8 cartridge
U38 port PLD, U42 PS/2 receiver
Placard main board
Decoupling: every chip's 100 nF Cn sits beside Un on its own sheet.
U22 pixel buffer, U23 line code
U16 color decoder, VGA
U17 instruction register PLD
U18 D register

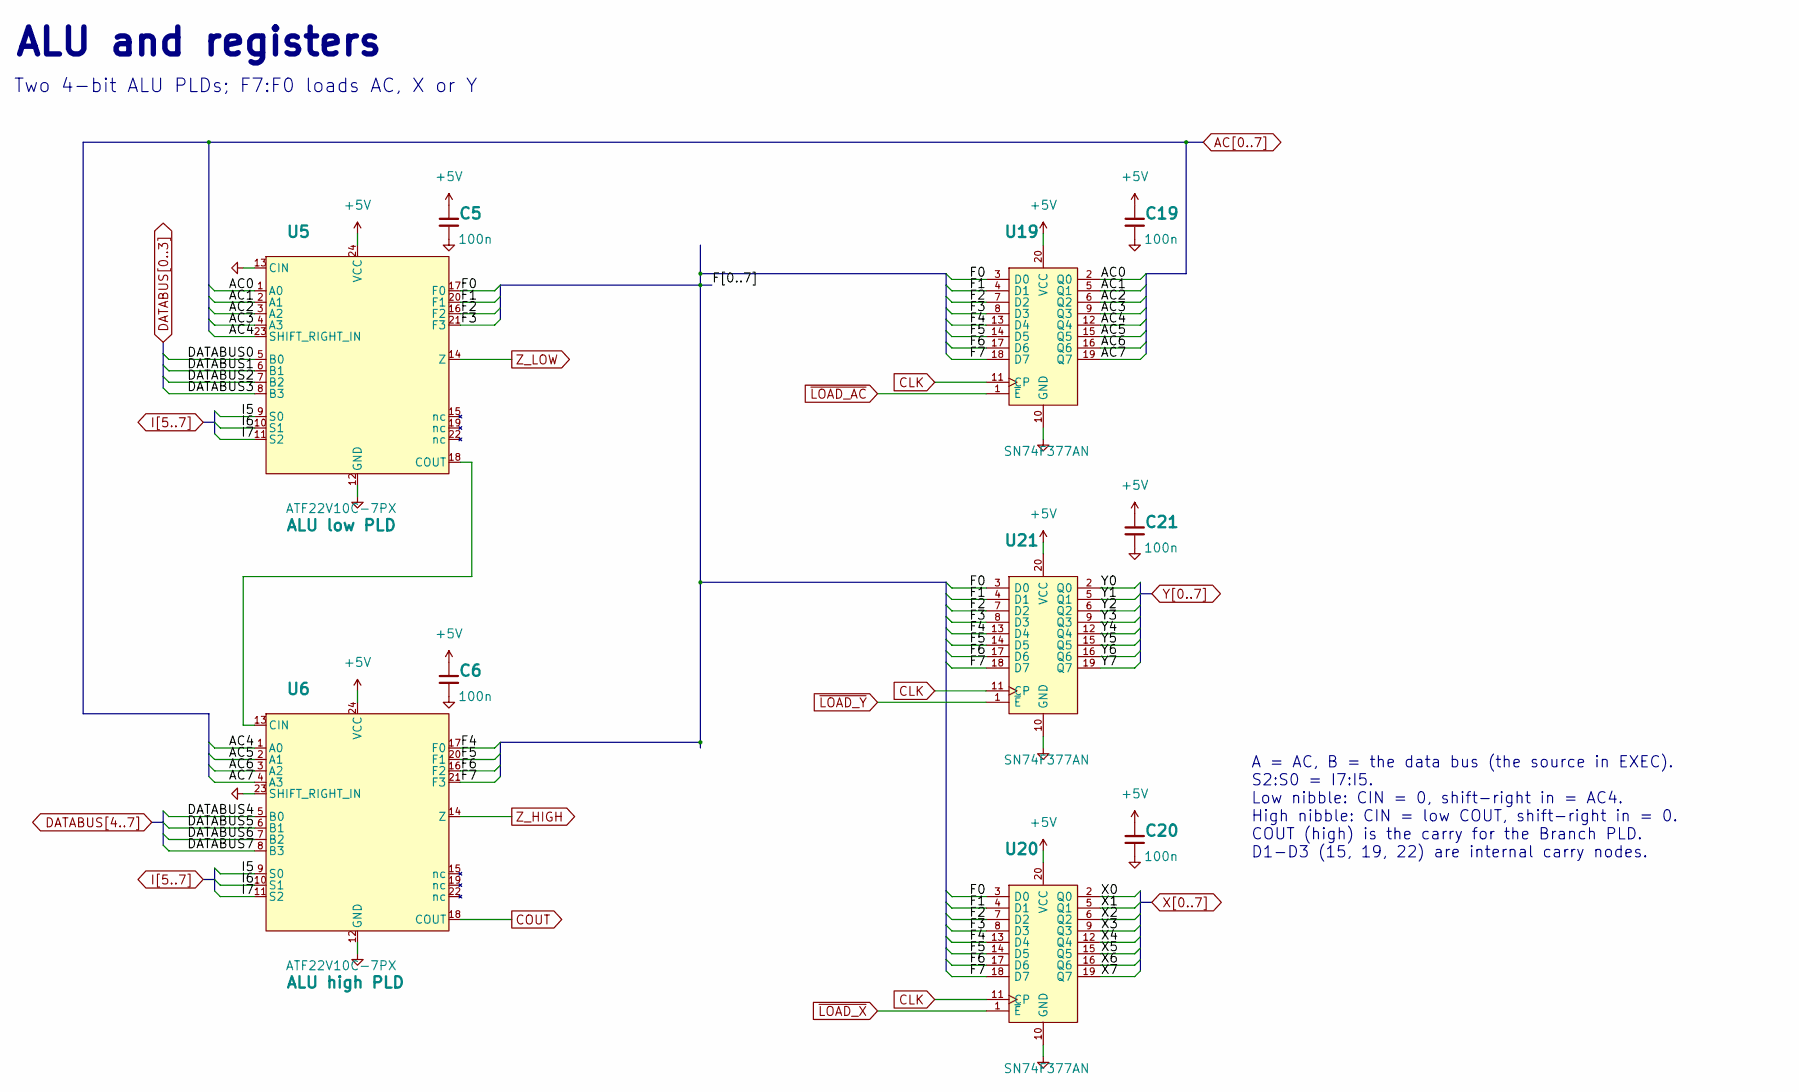
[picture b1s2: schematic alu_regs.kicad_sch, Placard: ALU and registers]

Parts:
C5, C6, C19, C20, C21: 100n; C_Disc_D5.0mm_W2.5mm_P5.00mm; MPN FG28X7R1H104KNT00
U5, U6: ATF22V10C-7PX; DIP-24_W7.62mm_Socket_Puller; MPN ATF22V10C-7PX
U19, U20, U21: SN74F377AN; DIP-20_W7.62mm_Socket_Puller; MPN SN74F377AN

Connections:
+5V: C5.1, C6.1, C19.1, C20.1, C21.1, U5.24 (VCC), U6.24 (VCC), U19.20 (VCC), U20.20 (VCC), U21.20 (VCC); also elsewhere on the board
/ALU and registers/F0: U5.17 (F0), U19.3 (D0), U20.3 (D0), U21.3 (D0)
/ALU and registers/F1: U5.20 (F1), U19.4 (D1), U20.4 (D1), U21.4 (D1)
/ALU and registers/F2: U5.16 (F2), U19.7 (D2), U20.7 (D2), U21.7 (D2)
/ALU and registers/F3: U5.21 (F3), U19.8 (D3), U20.8 (D3), U21.8 (D3)
/ALU and registers/F4: U6.17 (F0), U19.13 (D4), U20.13 (D4), U21.13 (D4)
/ALU and registers/F5: U6.20 (F1), U19.14 (D5), U20.14 (D5), U21.14 (D5)
/ALU and registers/F6: U6.16 (F2), U19.17 (D6), U20.17 (D6), U21.17 (D6)
/ALU and registers/F7: U6.21 (F3), U19.18 (D7), U20.18 (D7), U21.18 (D7)
AC0: U5.1 (A0), U19.2 (Q0); also elsewhere on the board
AC1: U5.2 (A1), U19.5 (Q1); also elsewhere on the board
AC2: U5.3 (A2), U19.6 (Q2); also elsewhere on the board
AC3: U5.4 (A3), U19.9 (Q3); also elsewhere on the board
AC4: U5.23 (SHIFT_RIGHT_IN), U6.1 (A0), U19.12 (Q4); also elsewhere on the board
AC5: U6.2 (A1), U19.15 (Q5); also elsewhere on the board
AC6: U6.3 (A2), U19.16 (Q6); also elsewhere on the board
AC7: U6.4 (A3), U19.19 (Q7); also elsewhere on the board
CLK: U19.11 (CP), U20.11 (CP), U21.11 (CP); also elsewhere on the board
COUT: U6.18 (COUT); also elsewhere on the board
DATABUS0: U5.5 (B0); also elsewhere on the board
DATABUS1: U5.6 (B1); also elsewhere on the board
DATABUS2: U5.7 (B2); also elsewhere on the board
DATABUS3: U5.8 (B3); also elsewhere on the board
DATABUS4: U6.5 (B0); also elsewhere on the board
DATABUS5: U6.6 (B1); also elsewhere on the board
DATABUS6: U6.7 (B2); also elsewhere on the board
DATABUS7: U6.8 (B3); also elsewhere on the board
GND: C5.2, C6.2, C19.2, C20.2, C21.2, U5.12 (GND), U5.13 (CIN), U6.12 (GND), U6.23 (SHIFT_RIGHT_IN), U19.10 (GND), U20.10 (GND), U21.10 (GND); also elsewhere on the board
I5: U5.9 (S0), U6.9 (S0); also elsewhere on the board
I6: U5.10 (S1), U6.10 (S1); also elsewhere on the board
I7: U5.11 (S2), U6.11 (S2); also elsewhere on the board
unnamed: U5.18 (COUT), U6.13 (CIN)
X0: U20.2 (Q0); also elsewhere on the board
X1: U20.5 (Q1); also elsewhere on the board
X2: U20.6 (Q2); also elsewhere on the board
X3: U20.9 (Q3); also elsewhere on the board
X4: U20.12 (Q4); also elsewhere on the board
X5: U20.15 (Q5); also elsewhere on the board
X6: U20.16 (Q6); also elsewhere on the board
X7: U20.19 (Q7); also elsewhere on the board
Y0: U21.2 (Q0); also elsewhere on the board
Y1: U21.5 (Q1); also elsewhere on the board
Y2: U21.6 (Q2); also elsewhere on the board
Y3: U21.9 (Q3); also elsewhere on the board
Y4: U21.12 (Q4); also elsewhere on the board
Y5: U21.15 (Q5); also elsewhere on the board
Y6: U21.16 (Q6); also elsewhere on the board
Y7: U21.19 (Q7); also elsewhere on the board
Z_HIGH: U6.14 (Z); also elsewhere on the board
Z_LOW: U5.14 (Z); also elsewhere on the board
~LOAD_AC: U19.1 (~E); also elsewhere on the board
~LOAD_X: U20.1 (~E); also elsewhere on the board
~LOAD_Y: U21.1 (~E); also elsewhere on the board

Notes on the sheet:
S2:S0 = I7:I5.
Low nibble: CIN = 0, shift-right in = AC4.
ALU and registers
High nibble: CIN = low COUT, shift-right in = 0.
Two 4-bit ALU PLDs; F7:F0 loads AC, X or Y
COUT (high) is the carry for the Branch PLD.
D1-D3 (15, 19, 22) are internal carry nodes.
A = AC, B = the data bus (the source in EXEC).

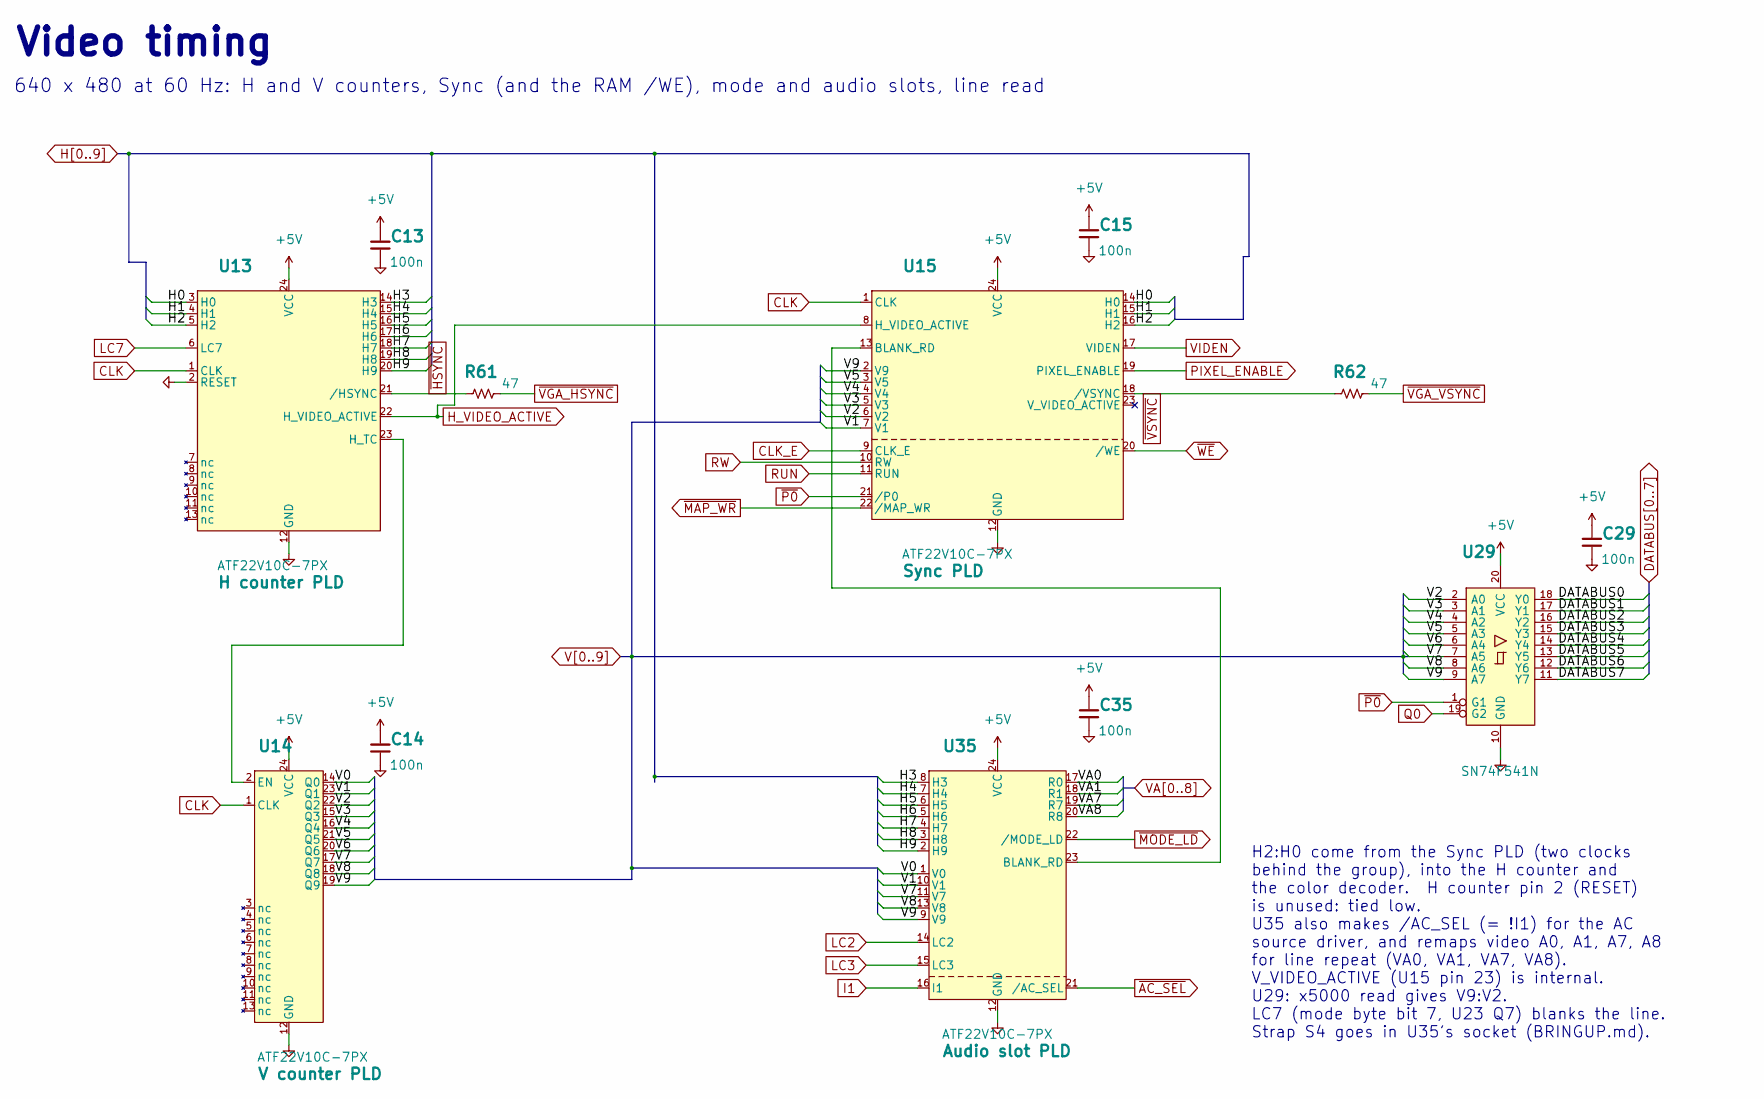
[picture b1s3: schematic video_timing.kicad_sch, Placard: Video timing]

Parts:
C13, C14, C15, C29, C35: 100n; C_Disc_D5.0mm_W2.5mm_P5.00mm; MPN FG28X7R1H104KNT00
R61, R62: 47; R_Axial_DIN0207_L6.3mm_D2.5mm_P10.16mm_Horizontal_Value; MPN MFR-25FBF52-47R
U13, U14, U15, U35: ATF22V10C-7PX; DIP-24_W7.62mm_Socket_Puller; MPN ATF22V10C-7PX
U29: SN74F541N; DIP-20_W7.62mm_Socket_Puller; MPN SN74F541N

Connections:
+5V: C13.1, C14.1, C15.1, C29.1, C35.1, U13.24 (VCC), U14.24 (VCC), U15.24 (VCC), U29.20 (VCC), U35.24 (VCC); also elsewhere on the board
CLK: U13.1 (CLK), U14.1 (CLK), U15.1 (CLK); also elsewhere on the board
CLK_E: U15.9 (CLK_E); also elsewhere on the board
DATABUS0: U29.18 (Y0); also elsewhere on the board
DATABUS1: U29.17 (Y1); also elsewhere on the board
DATABUS2: U29.16 (Y2); also elsewhere on the board
DATABUS3: U29.15 (Y3); also elsewhere on the board
DATABUS4: U29.14 (Y4); also elsewhere on the board
DATABUS5: U29.13 (Y5); also elsewhere on the board
DATABUS6: U29.12 (Y6); also elsewhere on the board
DATABUS7: U29.11 (Y7); also elsewhere on the board
GND: C13.2, C14.2, C15.2, C29.2, C35.2, U13.2 (RESET), U13.12 (GND), U14.12 (GND), U15.12 (GND), U29.10 (GND), U35.12 (GND); also elsewhere on the board
H0: U13.3 (H0), U15.14 (H0); also elsewhere on the board
H1: U13.4 (H1), U15.15 (H1); also elsewhere on the board
H2: U13.5 (H2), U15.16 (H2); also elsewhere on the board
H3: U13.14 (H3), U35.8 (H3); also elsewhere on the board
H4: U13.15 (H4), U35.7 (H4); also elsewhere on the board
H5: U13.16 (H5), U35.6 (H5); also elsewhere on the board
H6: U13.17 (H6), U35.5 (H6); also elsewhere on the board
H7: U13.18 (H7), U35.4 (H7); also elsewhere on the board
H8: U13.19 (H8), U35.3 (H8); also elsewhere on the board
H9: U13.20 (H9), U35.2 (H9); also elsewhere on the board
H_VIDEO_ACTIVE: U13.22 (H_VIDEO_ACTIVE), U15.8 (H_VIDEO_ACTIVE); also elsewhere on the board
I1: U35.16 (I1); also elsewhere on the board
LC2: U35.14 (LC2); also elsewhere on the board
LC3: U35.15 (LC3); also elsewhere on the board
LC7: U13.6 (LC7); also elsewhere on the board
unnamed: U13.23 (H_TC), U14.2 (EN)
unnamed: U15.13 (BLANK_RD), U35.23 (BLANK_RD)
PIXEL_ENABLE: U15.19 (PIXEL_ENABLE); also elsewhere on the board
Q0: U29.19 (G2); also elsewhere on the board
RUN: U15.11 (RUN); also elsewhere on the board
RW: U15.10 (RW); also elsewhere on the board
V0: U14.14 (Q0), U35.1 (V0)
V1: U14.23 (Q1), U15.7 (V1), U35.10 (V1)
V2: U14.22 (Q2), U15.6 (V2), U29.2 (A0); also elsewhere on the board
V3: U14.15 (Q3), U15.5 (V3), U29.3 (A1); also elsewhere on the board
V4: U14.16 (Q4), U15.4 (V4), U29.4 (A2); also elsewhere on the board
V5: U14.21 (Q5), U15.3 (V5), U29.5 (A3); also elsewhere on the board
V6: U14.20 (Q6), U29.6 (A4); also elsewhere on the board
V7: U14.17 (Q7), U29.7 (A5), U35.11 (V7)
V8: U14.18 (Q8), U29.8 (A6), U35.13 (V8)
V9: U14.19 (Q9), U15.2 (V9), U29.9 (A7), U35.9 (V9)
VA0: U35.17 (R0); also elsewhere on the board
VA1: U35.18 (R1); also elsewhere on the board
VA7: U35.19 (R7); also elsewhere on the board
VA8: U35.20 (R8); also elsewhere on the board
VIDEN: U15.17 (VIDEN); also elsewhere on the board
~AC_SEL: U35.21 (/AC_SEL); also elsewhere on the board
~HSYNC: R61.1, U13.21 (/HSYNC); also elsewhere on the board
~MAP_WR: U15.22 (nc); also elsewhere on the board
~MODE_LD: U35.22 (/MODE_LD); also elsewhere on the board
~P0: U15.21 (nc), U29.1 (G1); also elsewhere on the board
~VGA_HSYNC: R61.2; also elsewhere on the board
~VGA_VSYNC: R62.2; also elsewhere on the board
~VSYNC: R62.1, U15.18 (/VSYNC); also elsewhere on the board
~WE: U15.20 (/WE); also elsewhere on the board

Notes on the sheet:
U35 also makes /AC_SEL (= !I1) for the AC
640 x 480 at 60 Hz: H and V counters, Sync (and the RAM /WE), mode and audio slots, line read
LC7 (mode byte bit 7, U23 Q7) blanks the line.
U29: x5000 read gives V9:V2.
H2:H0 come from the Sync PLD (two clocks
behind the group), into the H counter and
V_VIDEO_ACTIVE (U15 pin 23) is internal.
source driver, and remaps video A0, A1, A7, A8
is unused: tied low.
the color decoder. H counter pin 2 (RESET)
for line repeat (VA0, VA1, VA7, VA8).
Strap S4 goes in U35's socket (BRINGUP.md).
Video timing

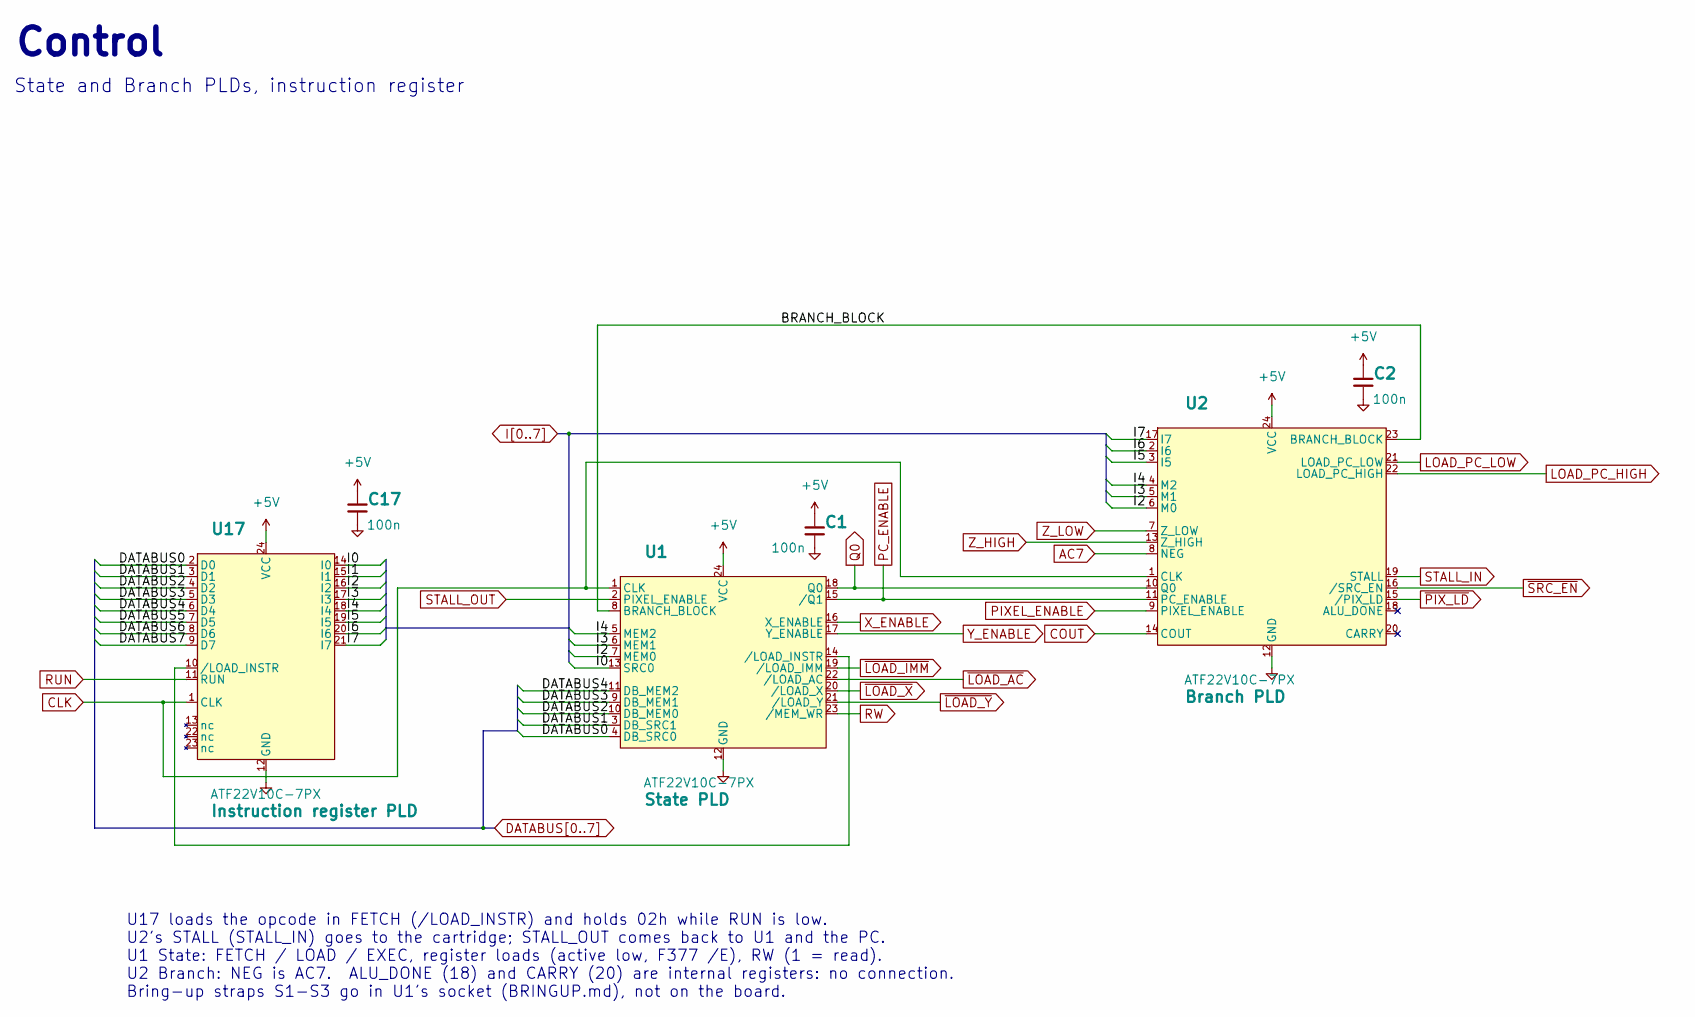
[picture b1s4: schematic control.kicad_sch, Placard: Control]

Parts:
C1, C2, C17: 100n; C_Disc_D5.0mm_W2.5mm_P5.00mm; MPN FG28X7R1H104KNT00
U1, U2, U17: ATF22V10C-7PX; DIP-24_W7.62mm_Socket_Puller; MPN ATF22V10C-7PX

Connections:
+5V: C1.1, C2.1, C17.1, U1.24 (VCC), U2.24 (VCC), U17.24 (VCC); also elsewhere on the board
/Control/BRANCH_BLOCK: U1.8 (BRANCH_BLOCK), U2.23 (BRANCH_BLOCK)
AC7: U2.8 (NEG); also elsewhere on the board
CLK: U1.1 (CLK), U2.1 (CLK), U17.1 (CLK); also elsewhere on the board
COUT: U2.14 (COUT); also elsewhere on the board
DATABUS0: U1.4 (DB_SRC0), U17.2 (D0); also elsewhere on the board
DATABUS1: U1.3 (DB_SRC1), U17.3 (D1); also elsewhere on the board
DATABUS2: U1.10 (DB_MEM0), U17.4 (D2); also elsewhere on the board
DATABUS3: U1.9 (DB_MEM1), U17.5 (D3); also elsewhere on the board
DATABUS4: U1.11 (DB_MEM2), U17.6 (D4); also elsewhere on the board
DATABUS5: U17.7 (D5); also elsewhere on the board
DATABUS6: U17.8 (D6); also elsewhere on the board
DATABUS7: U17.9 (D7); also elsewhere on the board
GND: C1.2, C2.2, C17.2, U1.12 (GND), U2.12 (GND), U17.12 (GND); also elsewhere on the board
I0: U1.13 (SRC0), U17.14 (I0)
I1: U17.15 (I1); also elsewhere on the board
I2: U1.7 (MEM0), U2.6 (M0), U17.16 (I2)
I3: U1.6 (MEM1), U2.5 (M1), U17.17 (I3)
I4: U1.5 (MEM2), U2.4 (M2), U17.18 (I4)
I5: U2.3 (I5), U17.19 (I5); also elsewhere on the board
I6: U2.2 (I6), U17.20 (I6); also elsewhere on the board
I7: U2.17 (I7), U17.21 (I7); also elsewhere on the board
LOAD_PC_HIGH: U2.22 (LOAD_PC_HIGH); also elsewhere on the board
LOAD_PC_LOW: U2.21 (LOAD_PC_LOW); also elsewhere on the board
unnamed: U1.14 (/LOAD_INSTR), U17.10 (/LOAD_INSTR)
PC_ENABLE: U1.15 (/Q1), U2.11 (PC_ENABLE); also elsewhere on the board
PIXEL_ENABLE: U2.9 (PIXEL_ENABLE); also elsewhere on the board
Q0: U1.18 (Q0), U2.10 (Q0); also elsewhere on the board
RUN: U17.11 (RUN); also elsewhere on the board
RW: U1.23 (/MEM_WR); also elsewhere on the board
STALL_IN: U2.19 (STALL); also elsewhere on the board
STALL_OUT: U1.2 (PIXEL_ENABLE); also elsewhere on the board
X_ENABLE: U1.16 (X_ENABLE); also elsewhere on the board
Y_ENABLE: U1.17 (Y_ENABLE); also elsewhere on the board
Z_HIGH: U2.13 (Z_HIGH); also elsewhere on the board
Z_LOW: U2.7 (Z_LOW); also elsewhere on the board
~LOAD_AC: U1.22 (/LOAD_AC); also elsewhere on the board
~LOAD_IMM: U1.19 (/LOAD_IMM); also elsewhere on the board
~LOAD_X: U1.20 (/LOAD_X); also elsewhere on the board
~LOAD_Y: U1.21 (/LOAD_Y); also elsewhere on the board
~PIX_LD: U2.15 (/PIX_LD); also elsewhere on the board
~SRC_EN: U2.16 (/SRC_EN); also elsewhere on the board

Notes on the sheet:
Bring-up straps S1-S3 go in U1's socket (BRINGUP.md), not on the board.
Control
U1 State: FETCH / LOAD / EXEC, register loads (active low, F377 /E), RW (1 = read).
U2 Branch: NEG is AC7. ALU_DONE (18) and CARRY (20) are internal registers: no connection.
U2's STALL (STALL_IN) goes to the cartridge; STALL_OUT comes back to U1 and the PC.
U17 loads the opcode in FETCH (/LOAD_INSTR) and holds 02h while RUN is low.
State and Branch PLDs, instruction register
